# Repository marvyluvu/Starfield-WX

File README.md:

<h1 align="center">StarField WX</h1>

<p align="center">
  <i>Portable Arduino‑powered dew‑risk weather station with LCD and LED halo.</i>
</p>

---

##  1. What is STARFIELD WX?

<p>
Starfield WX is a pocket-sized weather station that tells you when dew is about to become a problem for stargazing/ astrophotography.
</p>

---

##  2. Why did I make it?

<p>
I love being outside with my telescope, but because of where I live, I always end up with dew messing up my session before I could photograph anything. Starfield WX is my companion project for ORBTIZ. it can warn you about dew forming before it ruins your session.

---

##  3. How does it work?

The brains of the operation is the arduino uno. It:
- Reads temperature and humidity from a DHT11 module.
- Calculates an approximate dew point from those readings.
- Classifies dew risk (LOW, MEDIUM, HIGH) based on the spread between temperature and dew point.
- Shows live values on a 16×2 character LCD while auto‑cycling between temperature, humidity, and dew‑point screens.
- Uses a WS2812B LED halo as a status ring: green for low risk, orange for medium, red when dew is imminent.

---

##  4.Hardware schematic

<p>
You can view the full schematic for the ORBITZ PCB below.

The custom STARFIELD pcb plugs directly onto an Arduino Uno and breaks out all parts needed for weather station
</p>

key pins:
-  DHT11 data -> Arduino digital pin 2
-  WS2812B LED strip -> Arduino digital pin 6
-  1602 LCD (parallel) -> Arduino digital pins 7–12
-  Trimmer potentiometer -> LCD contrast
-  series resistors for the LCD backlight and LED strip data line

you can view the full schematic here.

---

##  5. How do you use it?

Power on the arduino uno via USB or a **5v** supply ( you can also power it using the usb hub on orbitz!!)

StarField WX boots, then starts cycling through three screens on the LCD:
  - Temperature in C
  - Relative humiditry in %
  - Dew point in C

The led halo color shows dew risk : green (low), orange ( medium), red (high).
when it turns red, conditions are close to the dew point and you should protect your optics or wrap up the session , unfortunately :( 

---
## 6. Assembly
Below is what the fully assembled design should look like.
1. Order all parts from the Starfield BOM.
2. Solder headers, resistors, the DHT11 module connector, LCD header, LED Strip header to the PCB.
3. Mount the potentiometer and adjust until the LCD text is clearly visible.
4. Attach the 1602 LCD to the enclosure using standoffs.
5. Cut the ws2812b strip to length and mount it arond the inside the top of the enclosure, then wire it to 5v, GND, and the data pin.
6. Insert the shield onto the Arduino Uno and secure the PCB into the enclosure.
7. Upload the code and enjoy!!

---

## 7. Firmware
The firmware is a single Arduino sketch that runs on the Uno

Features:

- Periodically reads DHT11 temperature and humidity
- computes dew point using a simple approximation formula
- cycle LCD screens every few seconds (temperature, humidty, dew point)
- computes dew risk catergory and updates the LED halo color

## how to flash
1. open firmware/starfield_wx.ino in the arduino IDE
2. select arduino uno as the board and choose the correct serial port
3. Install these libraries (DHT11, NEOPIXELS, LIQUID CRYSTALS) - (see [Arduino Library Installation Guide](https://docs.arduino.cc/software/ide-v1/tutorials/installing-libraries/) to know how to install libraries)
5. click upload.
6. after reseting, the splash screen appears, then live readings start
Feel free to tweak the threshold and LED colors to match your local climate and conditions

##  8. Images

<table>
  <tr>
    <td align="center">
      <strong>FINAL PCB SCREENSHOTS</strong><br><br>
      
    </td>
  </tr>
  <tr>
    <td align="center">
      <strong>PCB</strong><br><br>
      
    </td>
  </tr>
  <tr>
    <td align="center">
      <strong>FINAL BUILD</strong><br><br>
      
    </td>
  </tr>
</table>

##  8. Bill of Materials (BOM)

The full detailed BOM is included in this repository:

- [[`/STARFIELD_BILL_OF_MATERIALS.csv`](https://github.com/marvyluvu/Starfield-WX/blob/69a2b140c6205f69048c935fe2e7507fc950f91d/hardware/STARFIELD_BOM.csv)

You can open this file in Excel, Google Sheets, or any spreadsheet tool.
It includes part names, descriptions, quantities, prices, and direct purchase links.

Key components

### Full BOM (summary)

### Full BOM (summary)

| Product name | Description | Qty | Unit price | Link |
|-------------|-------------|-----|-----------|------|
| Arduino Uno | Main microcontroller board | 1 | dh30.90 | [Amazon](https://www.amazon.ae/UNO-ATmega328P-Development-Straight-Developer/dp/B07PFCGYRS/) |
| WS2812B RGB STRIP | led halo indicator | 1 | dh3.75 | [AliExpress](https://ar.aliexpress.com/item/1005005537967685.html) |
| jumper cables | for connecting components internally | 1 | dh12.45 | [AliExpress](https://www.aliexpress.com/ssr/300000512/BundleDeals2?productIds=1005003641187997%3A12000026613929397) |
| STARFIELD custom pcb | main board | 1 | dh108.67 | JLCPCB |
| MALE HEADERS | LED , DHT11 PINS | 1 | dh3.75 | [AliExpress](https://ar.aliexpress.com/item/1005001514058091.html) |
| DHT11 MODULE | HUMIDTY AND TEMP SENSOR | 1 | dh17.48 | [AliExpress](https://ar.aliexpress.com/item/1005012263106656.html) |
| 1602A LCD Display | Main Display | 1 | dh65.88 | [Amazon](https://www.amazon.ae/naughtystarts-Character-Controller-Blacklight-Compatible/dp/B0B1QFDJ3Y/) |
| Trimmer potentiometer | Controls display contrast (3296W-103 10K) | 1 | dh10.90 | [AliExpress](https://ar.aliexpress.com/item/1005012099171886.html) |
| 220 OHM RESISTOR | lcd backlight resistor 220 OHM | 1 | dh3.75 | [AliExpress](https://ar.aliexpress.com/item/1005004002774546.html) |
| 330 OHM RESISTOR | led strip resistor 330 OHM | 1 | dh3.75 | [AliExpress](https://ar.aliexpress.com/item/1005004002774546.html) |

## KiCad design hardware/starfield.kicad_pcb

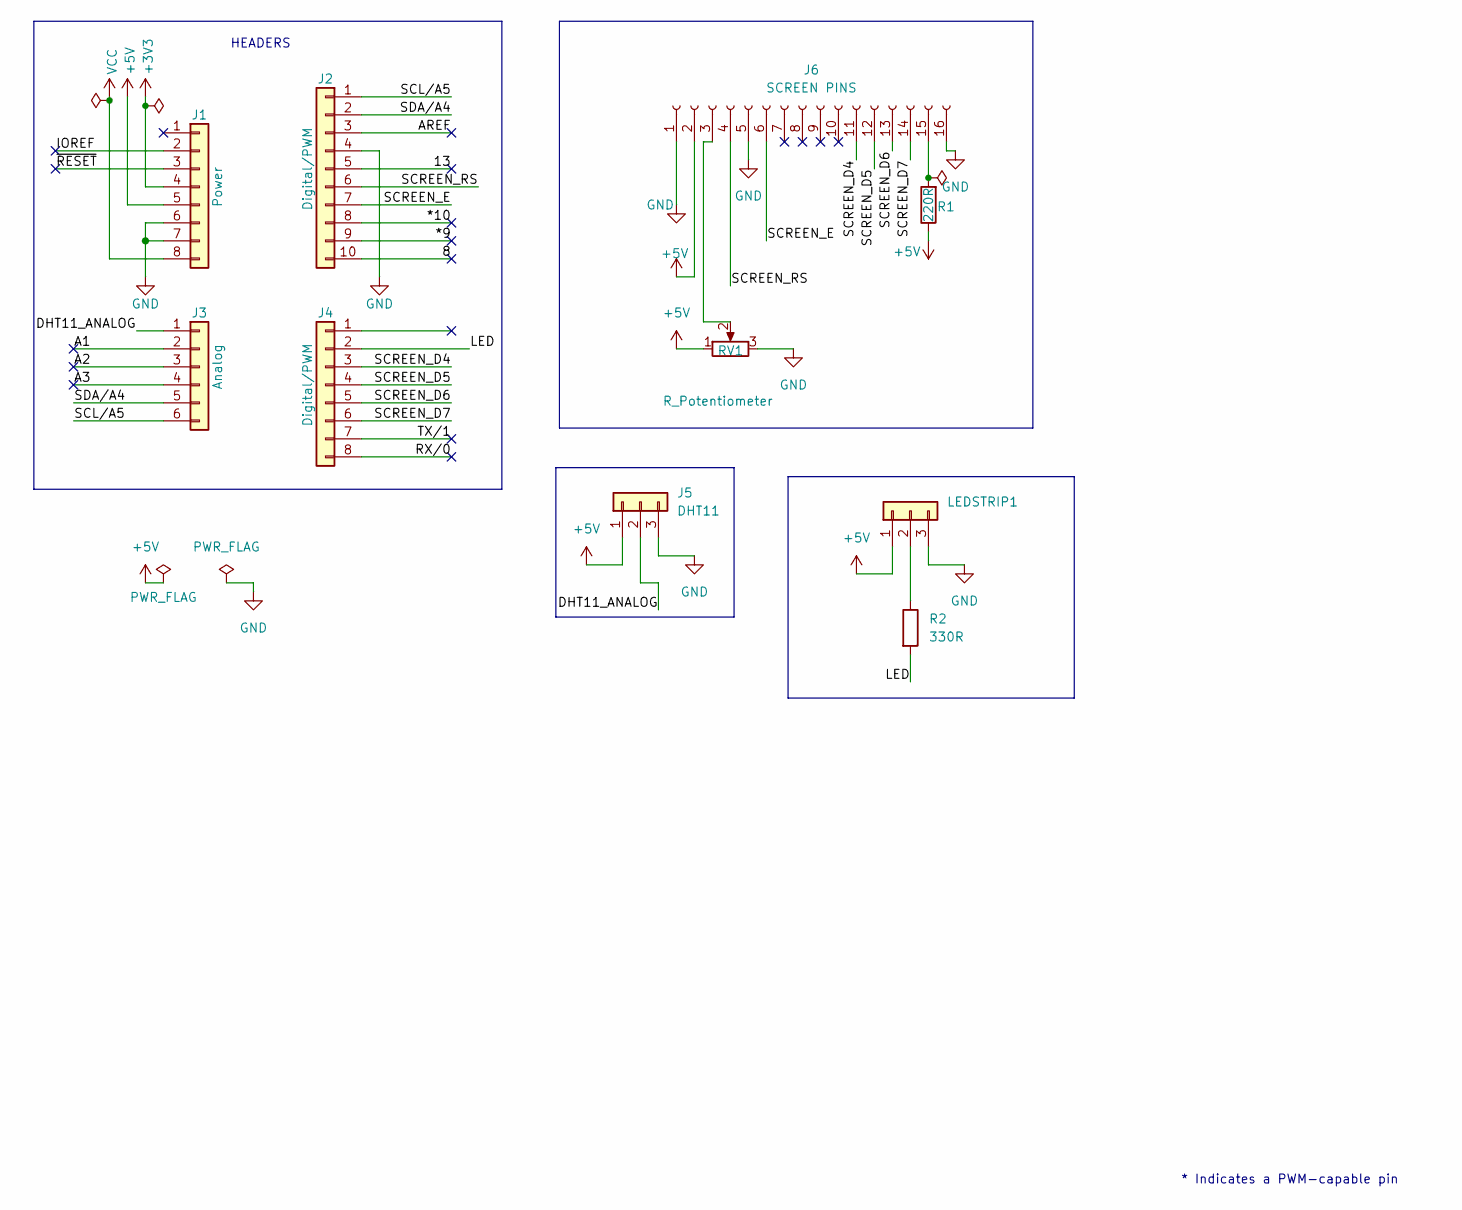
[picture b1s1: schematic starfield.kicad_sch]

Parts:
J1: Power; PinSocket_1x08_P2.54mm_Vertical
J2: Digital/PWM; PinSocket_1x10_P2.54mm_Vertical
J3: Analog; PinSocket_1x06_P2.54mm_Vertical
J4: Digital/PWM; PinSocket_1x08_P2.54mm_Vertical
J5: DHT11; PinHeader_1x03_P2.54mm_Vertical
J6: SCREEN PINS; PinSocket_1x16_P2.54mm_Vertical
LEDSTRIP1: LEDSTRIP1; PinHeader_1x03_P2.54mm_Vertical
R1: 220R; R_Axial_DIN0207_L6.3mm_D2.5mm_P7.62mm_Horizontal
R2: 330R; R_Axial_DIN0207_L6.3mm_D2.5mm_P7.62mm_Horizontal
RV1: R_Potentiometer; Potentiometer_Bourns_3296W_Vertical

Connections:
+3V3: J1.4
+5V: J1.5, J5.1, J6.2, LEDSTRIP1.1, R1.1, RV1.1
/8: J2.10
/13: J2.5
/*9: J2.9
/*10: J2.8
/A1: J3.2
/A2: J3.3
/A3: J3.4
/AREF: J2.3
/DHT11_ANALOG: J3.1, J5.2
/IOREF: J1.2
/LED: J4.2, R2.2
/RX/0: J4.8
/SCL/A5: J2.1, J3.6
/SCREEN_D4: J4.3, J6.11
/SCREEN_D5: J4.4, J6.12
/SCREEN_D6: J4.5, J6.13
/SCREEN_D7: J4.6, J6.14
/SCREEN_E: J2.7, J6.6
/SCREEN_RS: J2.6, J6.4
/SDA/A4: J2.2, J3.5
/TX/1: J4.7
/~RESET: J1.3
GND: J1.6, J1.7, J2.4, J5.3, J6.1, J6.5, J6.16, LEDSTRIP1.3, RV1.3
unnamed: J6.3, RV1.2
unnamed: J6.15, R1.2
unnamed: LEDSTRIP1.2, R2.1
VCC: J1.8

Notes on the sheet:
HEADERS
* Indicates a PWM-capable pin

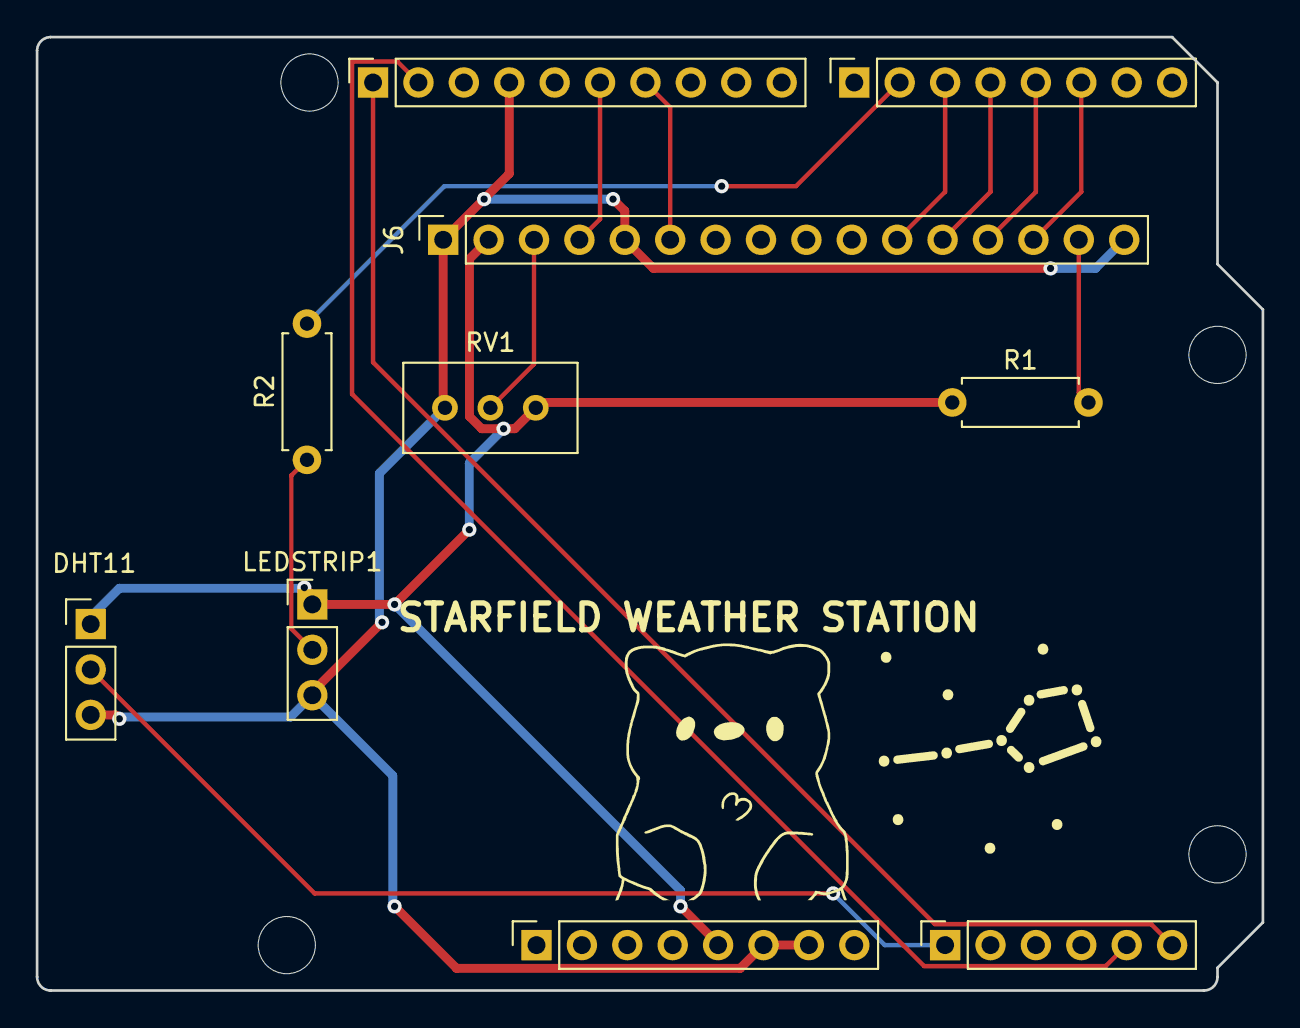
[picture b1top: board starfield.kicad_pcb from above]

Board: 2 copper layers, 68.6 x 53.3 mm, 14 parts (0 on the bottom side), 15 nets.

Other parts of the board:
MH1, MH2, MH3, MH4: MountingHole_3.2mm

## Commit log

2026-06-20 Rename STARFIELD ASSEMBLED.png to STARFIELD_ASSEMBLED.png
2026-06-20 Rename STARFIELD BOM.csv to STARFIELD_BOM.csv
2026-06-20 Rename ORBITZ - STARFIELD BOM.csv to STARFIELD_BOM.csv
2026-06-20 Fix image filename in README.md
2026-06-20 Fix formatting and capitalization in README.md
    Updated text formatting and corrected capitalization in the README file.
2026-06-22 Refactor key pins list in README.md
    Updated key pins section for clarity and consistency.
